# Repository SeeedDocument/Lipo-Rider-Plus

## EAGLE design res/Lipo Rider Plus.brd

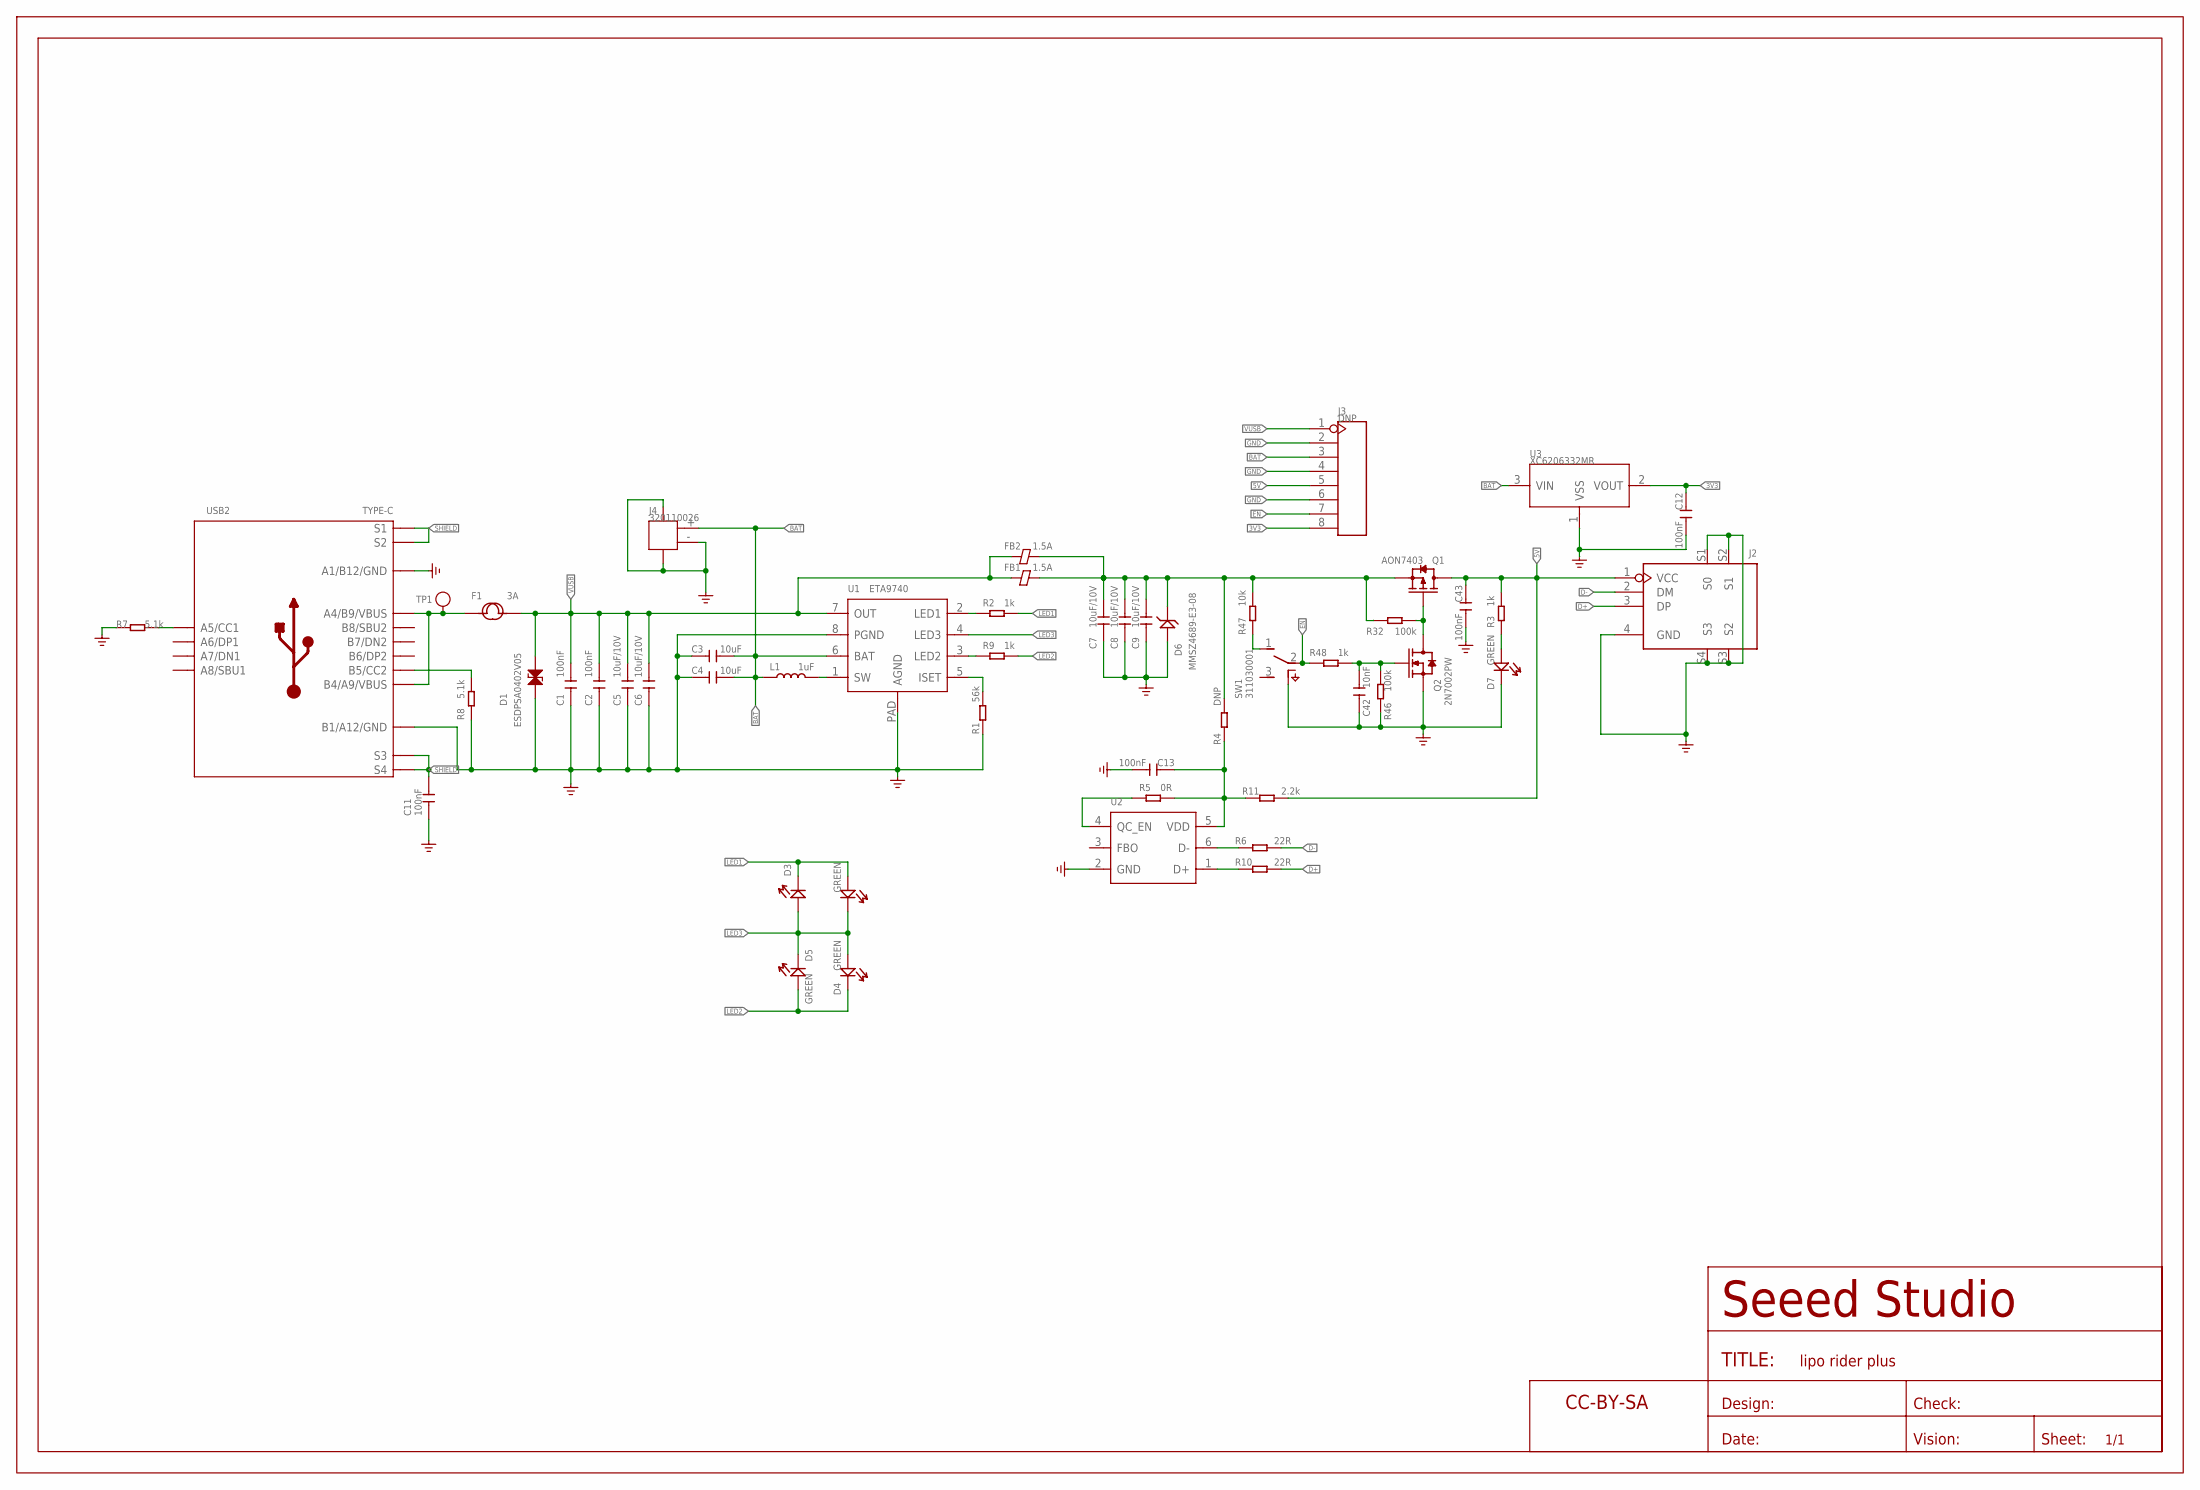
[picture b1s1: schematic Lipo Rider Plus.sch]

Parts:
C1, C2, C11, C12, C13, C43: 100nF; C0402
C3, C4: 10uF; C0603
C5, C6, C7, C8, C9: 10uF/10V; C0805
C42: 10nF; C0402
D1: ESDPSA0402V05; ESD-0402
D2, D3, D4, D5, D7: GREEN; LED-0402
D6: MMSZ4689-E3-08; SOD-123
F1: 3A; F1812
FB1, FB2: 1.5A; F0805
FR1: SEEEDSTUDIO-OPEN-SCH-FRAME-BIG; SEEEDSTUDIO-PCB-FRAME
J2: USB4+4P-SMD+DIP; USB4+4P-2.0-14.6X10.6X5.72MM
J3: DNP; H8-2.54-C65D35MIL
J4: 320110026; HW2-SMD-2.0-90D
L1: 1uF; L4.4X3.0MM
Q1: AON7403; DFN8P-0.65-3X3X0.8MM
Q2: 2N7002PW; SOT-323
R1: 56k; R0402
R2, R3, R9, R48: 1k; R0402
R4: DNP; R0402
R5: 0R; R0402
R6, R10: 22R; R0402
R7, R8: 5.1k; R0402
R11: 2.2k; R0402
R32, R46: 100k; R0402
R47: 10k; R0402
SW1: 311030001; SW7-SMD-L6.7X2.7X3.2MM
TP1: TEST; TP-D45MIL
U1: ETA9740; ESOP8L-1.27-5X3.9MM
U2: CONTROLLER-FP6601Q; SOT-23-6
U3: XC6206332MR; SOT-23
USB2: TYPE-C; USB2.0-TYPE-C

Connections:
3V3: C12.1, J3.8, U3.2 (VOUT)
5V: C43.1, J2.1 (VCC), J3.5, Q1.5 (D), Q1.6 (D), Q1.7 (D), Q1.8 (D), Q1.9 (D), R3.2, R11.2
BAT: C3.1, C4.1, J3.3, J4.+ (1), L1.1, U1.6 (BAT), U3.3 (VIN)
D+: J2.3 (DP), R10.2
D-: J2.2 (DM), R6.2
EN: J3.7, R48.1, SW1.2 (COM)
GND: C1.2, C2.2, C3.2, C4.2, C5.1, C6.1, C7.1, C8.1, C9.1, C11.2, C12.2, C13.2, C42.2, C43.2, D1.1, D6.+, D7.-, J2.4 (GND), J2.S1 (S0), J2.S2 (S1), J2.S3 (S2), J2.S4 (S3), J3.2, J3.4, J3.6, J4.3, J4.4, J4.- (2), Q2.2 (S), R1.1, R7.1, R8.2, R46.1, SW1.SS1 (SS2), SW1.SS2, SW1.SS3 (SS2), SW1.SS4 (SS2), U1.8 (PGND), U1.PAD (AGND), U2.2 (GND), U3.1 (VSS), USB2.A1_B12 (A1/B12/GND), USB2.B1_A12 (B1/A12/GND)
LED1: D2.+, D3.-, R2.2
LED2: D4.-, D5.+, R9.2
LED3: D2.-, D3.+, D4.+, D5.-, U1.4 (LED3)
unnamed: R7.2, USB2.A5 (A5/CC1)
unnamed: R8.1, USB2.B5 (B5/CC2)
unnamed: R47.1, SW1.1 (A)
unnamed: F1.1, TP1.T, USB2.A4_B9 (A4/B9/VBUS), USB2.B4_A9 (B4/A9/VBUS)
unnamed: D7.+, R3.1
unnamed: R1.2, U1.5 (ISET)
unnamed: L1.2, U1.1 (SW)
unnamed: R9.1, U1.3 (LED2)
unnamed: R5.1, U2.4 (QC_EN)
unnamed: C13.1, R4.1, R5.2, R11.1, U2.5 (VDD)
unnamed: R2.1, U1.2 (LED1)
unnamed: R6.1, U2.6 (D-)
unnamed: R10.1, U2.1 (D+)
unnamed: Q1.4 (G), Q2.3 (D), R32.2
unnamed: C42.1, Q2.1 (G), R46.2, R48.2
SHIELD: C11.1, USB2.S1, USB2.S2, USB2.S3, USB2.S4, USB2.S5 (S1), USB2.S6 (S2)
VCC_5V: C7.2, C8.2, C9.2, D6.-, FB1.2, FB2.2, Q1.1 (S), Q1.2 (S), Q1.3 (S), R4.2, R32.1, R47.2
VUSB: C1.1, C2.1, C5.2, C6.2, D1.2, F1.2, FB1.1, FB2.1, J3.1, U1.7 (OUT)

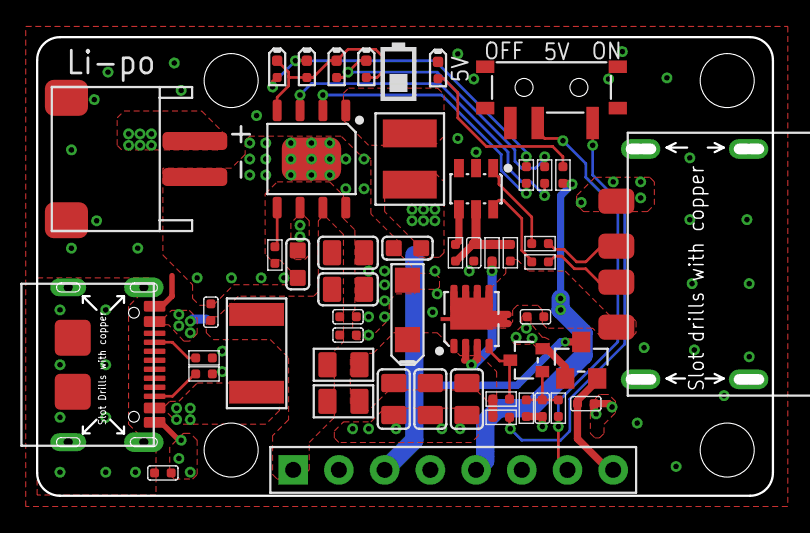
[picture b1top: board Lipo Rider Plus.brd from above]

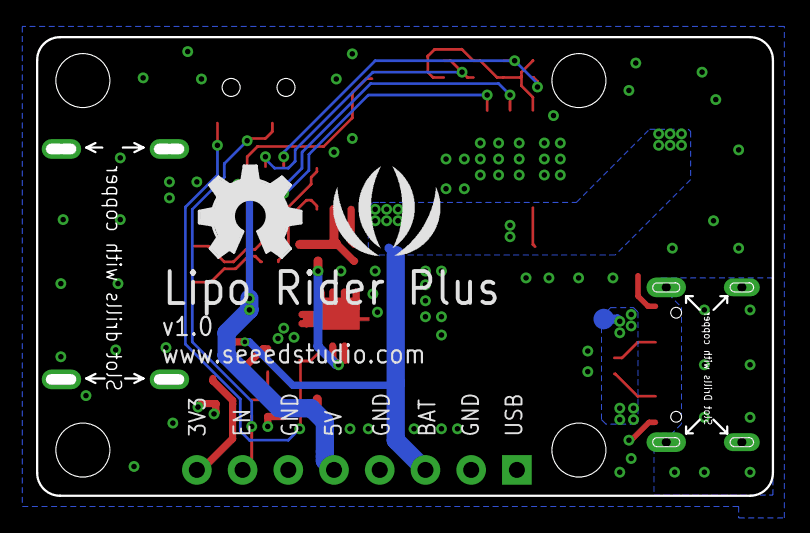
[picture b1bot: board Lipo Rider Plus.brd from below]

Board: 2 copper layers, 40.4 x 25.0 mm, 54 parts (3 on the bottom side), 28 nets.

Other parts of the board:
U$1: SEEED-SILK-TNAME-280*268MIL
U$2: OSHW_FILLX200_NOTEXT_TNAME

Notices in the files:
parts and their libraries:
moudle-new: This work is licensed under the Creative Commons Attribution 4.0 International License.
To view a copy of this license,visit:
http://creativecommons.org/licenses/by-sa/4.0
moudle-new: CC-BY-SA
